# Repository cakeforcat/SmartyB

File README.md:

# SmartyB aka Smart Button(s)
4 button panel for use with ESPhome. Powered by mains AC, 2 relay switch channels, fits in a UK light switch box.
## Photos

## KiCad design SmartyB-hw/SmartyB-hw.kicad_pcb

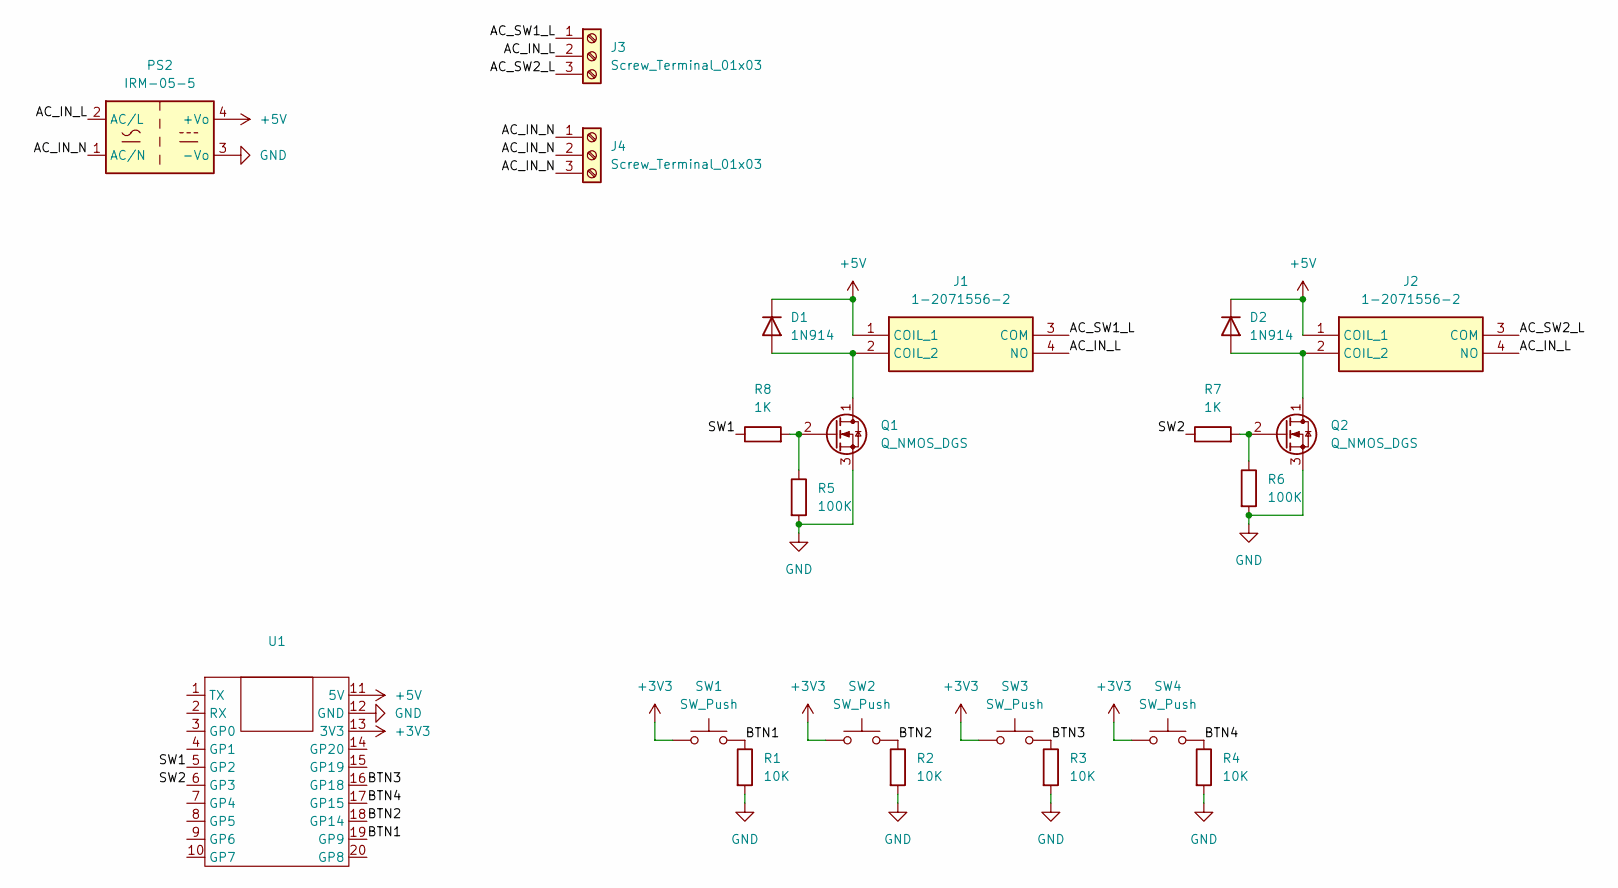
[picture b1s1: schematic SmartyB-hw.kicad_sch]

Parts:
D1, D2: 1N914; D_DO-35_SOD27_P7.62mm_Horizontal
J1, J2: 1-2071556-2; 120715562; Mouser Part Number 655-1-2071556-2
J3, J4: Screw_Terminal_01x03; TerminalBlock_RND_205-00046_1x03_P5.00mm_Horizontal
PS2: IRM-05-5; Converter_ACDC_MeanWell_IRM-05-xx_THT
Q1, Q2: Q_NMOS_DGS; TO-92
R1, R2, R3, R4: 10K; R_Axial_DIN0204_L3.6mm_D1.6mm_P5.08mm_Horizontal
R5, R6: 100K; R_Axial_DIN0204_L3.6mm_D1.6mm_P5.08mm_Horizontal
R7, R8: 1K; R_Axial_DIN0204_L3.6mm_D1.6mm_P5.08mm_Horizontal
SW1, SW2, SW3, SW4: SW_Push; SW_PUSH_6mm_H5mm
U1: ESP32_C6_SUPERMINI

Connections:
+3V3: SW1.1, SW2.1, SW3.1, SW4.1, U1.13 (3V3)
+5V: D1.1 (K), D2.1 (K), J1.1 (COIL_1), J2.1 (COIL_1), PS2.4 (+Vo), U1.11 (5V)
/AC_IN_L: J1.4 (NO), J2.4 (NO), J3.2, PS2.2 (AC/L)
/AC_IN_N: J4.1, J4.2, J4.3, PS2.1 (AC/N)
/AC_SW1_L: J1.3 (COM), J3.1
/AC_SW2_L: J2.3 (COM), J3.3
/BTN1: R1.1, SW1.2, U1.19 (GP9)
/BTN2: R2.1, SW2.2, U1.18 (GP14)
/BTN3: R3.1, SW3.2, U1.16 (GP18)
/BTN4: R4.1, SW4.2, U1.17 (GP15)
/SW1: R8.1, U1.5 (GP2)
/SW2: R7.1, U1.6 (GP3)
GND: PS2.3 (-Vo), Q1.3 (S), Q2.3 (S), R1.2, R2.2, R3.2, R4.2, R5.2, R6.2, U1.12 (GND)
unnamed: D1.2 (A), J1.2 (COIL_2), Q1.1 (D)
unnamed: D2.2 (A), J2.2 (COIL_2), Q2.1 (D)
unnamed: Q1.2 (G), R5.1, R8.2
unnamed: Q2.2 (G), R6.1, R7.2

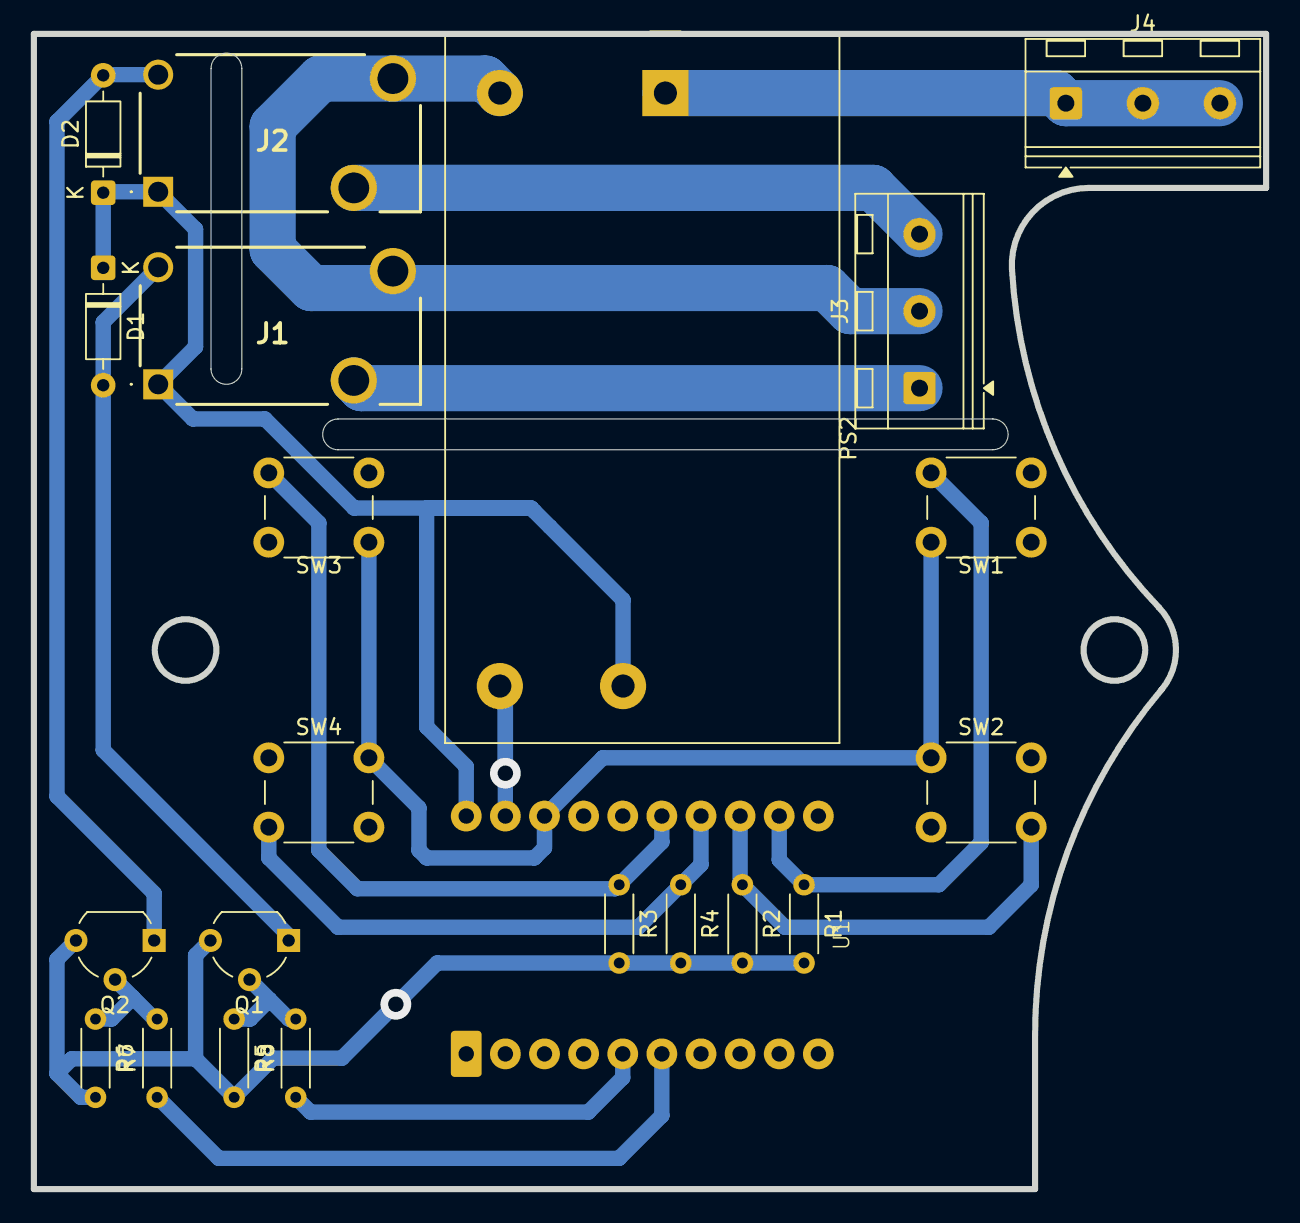
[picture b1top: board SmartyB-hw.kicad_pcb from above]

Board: 2 copper layers, 80.0 x 75.0 mm, 22 parts (0 on the bottom side), 17 nets.

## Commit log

2026-03-04 init hw
2026-03-04 move some hw stuff
2026-03-04 some moar hw stuff
2026-03-04 hw gerbers
2026-03-05 hw minor adjustment
2026-03-05 hw pcb outline change
2026-03-06 hw revisionssss
2026-03-07 hw revisionssss2
2026-03-09 change psu, add some 3d
2026-03-17 idk hw or smth
2026-03-17 gerbers
2026-03-18 readme
2026-04-05 readme + kicad10
2026-04-05 enclosure
